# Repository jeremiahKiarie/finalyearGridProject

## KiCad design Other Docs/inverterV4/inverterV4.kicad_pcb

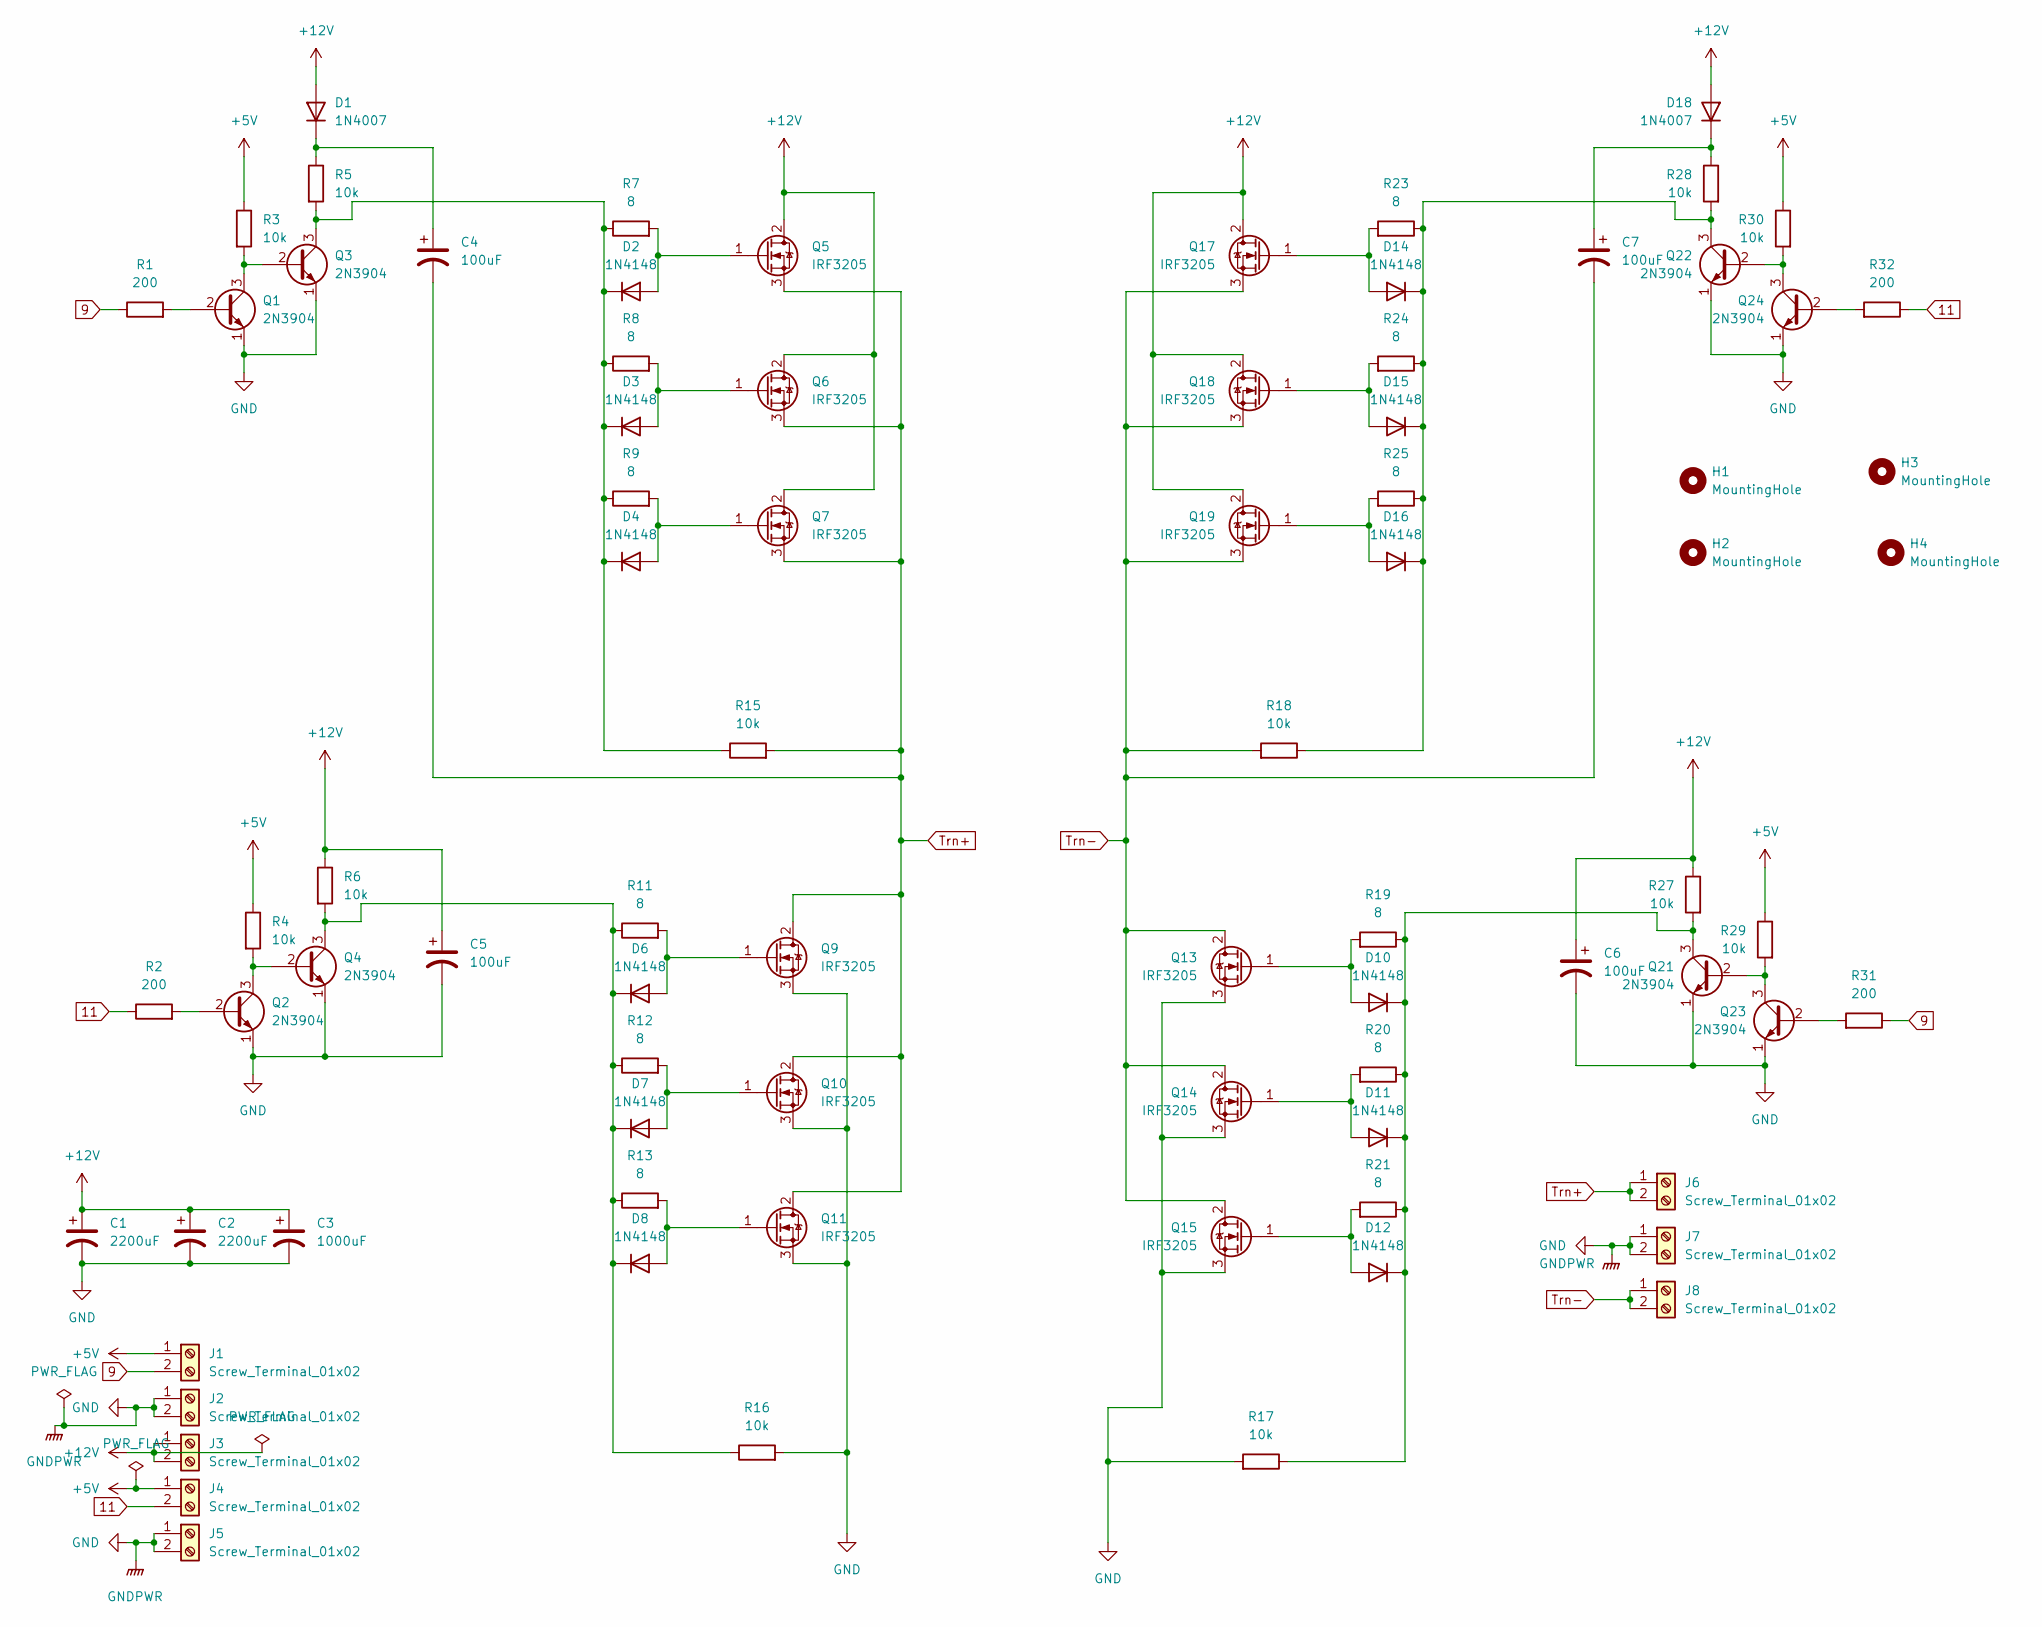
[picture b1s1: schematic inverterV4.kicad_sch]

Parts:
C1, C2: 2200uF; CP_Radial_D17.0mm_P7.50mm
C3: 1000uF; CP_Radial_D13.0mm_P5.00mm
C4, C5, C6, C7: 100uF; CP_Radial_D6.3mm_P2.50mm
D1, D18: 1N4007; D_DO-41_SOD81_P10.16mm_Horizontal
D2, D3, D4, D6, D7, D8, D10, D11, D12, D14, D15, D16: 1N4148; D_DO-35_SOD27_P10.16mm_Horizontal
H1, H2, H3, H4: MountingHole; MountingHole_4mm
J1, J2, J3, J4, J5, J6, J7, J8: Screw_Terminal_01x02; TerminalBlock_Phoenix_MKDS-3-2-5.08_1x02_P5.08mm_Horizontal
Q1, Q2, Q3, Q4, Q21, Q22, Q23, Q24: 2N3904; TO-92_Inline_Wide
Q5, Q6, Q7, Q9, Q10, Q11, Q13, Q14, Q15, Q17, Q18, Q19: IRF3205; TO-220-3_Vertical
R1, R2, R31, R32: 200; R_Axial_DIN0207_L6.3mm_D2.5mm_P10.16mm_Horizontal
R3, R4, R5, R6, R15, R16, R17, R18, R27, R28, R29, R30: 10k; R_Axial_DIN0309_L9.0mm_D3.2mm_P15.24mm_Horizontal
R7, R8, R9, R11, R12, R13, R19, R20, R21, R23, R24, R25: 8; R_Axial_DIN0309_L9.0mm_D3.2mm_P15.24mm_Horizontal

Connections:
9: J1.2, R1.1, R31.1
11: J4.2, R2.1, R32.1
+5V: J1.1, J4.1, R3.1, R4.1, R29.1, R30.1
+12V: C1.1, C2.1, C3.1, C5.1, C6.1, D1.2 (A), D18.2 (A), J3.1, J3.2, Q5.2 (D), Q6.2 (D), Q7.2 (D), Q17.2 (D), Q18.2 (D), Q19.2 (D), R6.1, R27.1
GND: C1.2, C2.2, C3.2, C5.2, C6.2, J2.1, J2.2, J5.1, J5.2, J7.1, J7.2, Q1.1 (E), Q2.1 (E), Q3.1 (E), Q4.1 (E), Q9.3 (S), Q10.3 (S), Q11.3 (S), Q13.3 (S), Q14.3 (S), Q15.3 (S), Q21.1 (E), Q22.1 (E), Q23.1 (E), Q24.1 (E), R16.2, R17.2
unnamed: C4.1, D1.1 (K), R5.1
unnamed: C7.1, D18.1 (K), R28.1
unnamed: D2.1 (K), D3.1 (K), D4.1 (K), Q3.3 (C), R5.2, R7.1, R8.1, R9.1, R15.1
unnamed: D2.2 (A), Q5.1 (G), R7.2
unnamed: D3.2 (A), Q6.1 (G), R8.2
unnamed: D4.2 (A), Q7.1 (G), R9.2
unnamed: D6.1 (K), D7.1 (K), D8.1 (K), Q4.3 (C), R6.2, R11.1, R12.1, R13.1, R16.1
unnamed: D6.2 (A), Q9.1 (G), R11.2
unnamed: D7.2 (A), Q10.1 (G), R12.2
unnamed: D8.2 (A), Q11.1 (G), R13.2
unnamed: D10.1 (K), D11.1 (K), D12.1 (K), Q21.3 (C), R17.1, R19.1, R20.1, R21.1, R27.2
unnamed: D10.2 (A), Q13.1 (G), R19.2
unnamed: D11.2 (A), Q14.1 (G), R20.2
unnamed: D12.2 (A), Q15.1 (G), R21.2
unnamed: D14.1 (K), D15.1 (K), D16.1 (K), Q22.3 (C), R18.1, R23.1, R24.1, R25.1, R28.2
unnamed: D14.2 (A), Q17.1 (G), R23.2
unnamed: D15.2 (A), Q18.1 (G), R24.2
unnamed: D16.2 (A), Q19.1 (G), R25.2
unnamed: Q1.2 (B), R1.2
unnamed: Q1.3 (C), Q3.2 (B), R3.2
unnamed: Q2.2 (B), R2.2
unnamed: Q2.3 (C), Q4.2 (B), R4.2
unnamed: Q21.2 (B), Q23.3 (C), R29.2
unnamed: Q22.2 (B), Q24.3 (C), R30.2
unnamed: Q23.2 (B), R31.2
unnamed: Q24.2 (B), R32.2
Trn+: C4.2, J6.1, J6.2, Q5.3 (S), Q6.3 (S), Q7.3 (S), Q9.2 (D), Q10.2 (D), Q11.2 (D), R15.2
Trn-: C7.2, J8.1, J8.2, Q13.2 (D), Q14.2 (D), Q15.2 (D), Q17.3 (S), Q18.3 (S), Q19.3 (S), R18.2

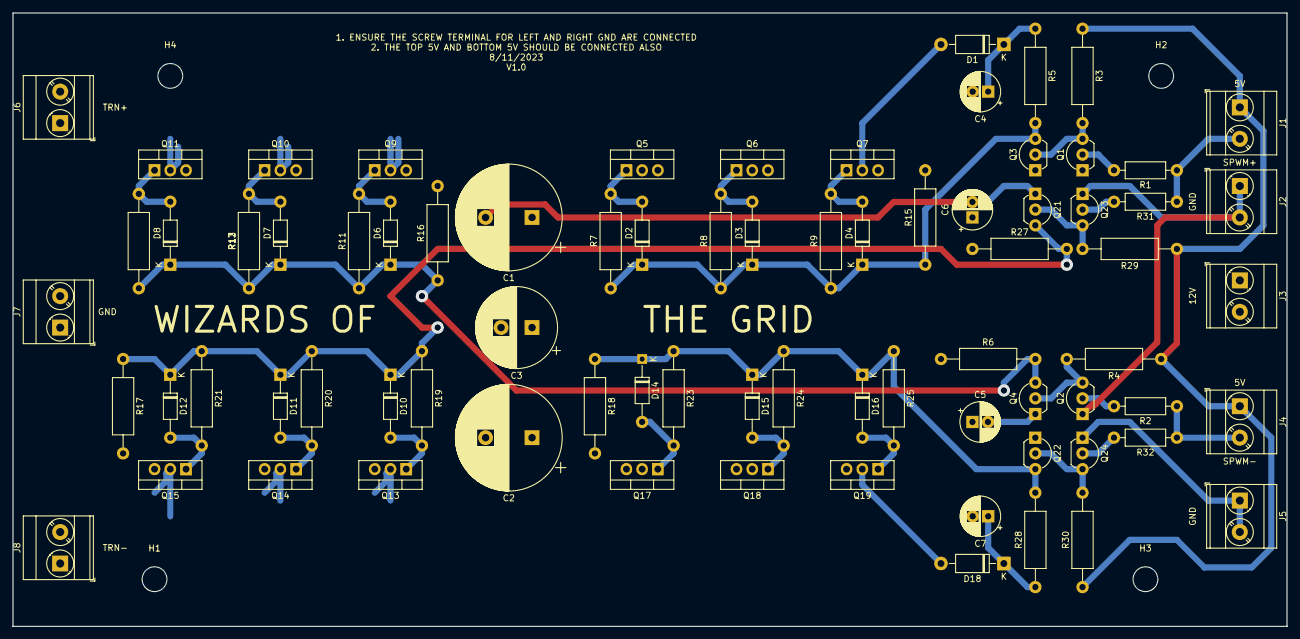
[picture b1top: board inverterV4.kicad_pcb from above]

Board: 2 copper layers, 205.7 x 99.1 mm, 81 parts (0 on the bottom side), 33 nets.

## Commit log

2023-12-03 first draft, comm and caes control
2023-12-10 complete code version 1, not tested
2023-12-14 HMI Formatting
2024-01-18 add solar panel report
2024-01-19 added uC SPWM generator program
2024-01-19 add inverter PCB
